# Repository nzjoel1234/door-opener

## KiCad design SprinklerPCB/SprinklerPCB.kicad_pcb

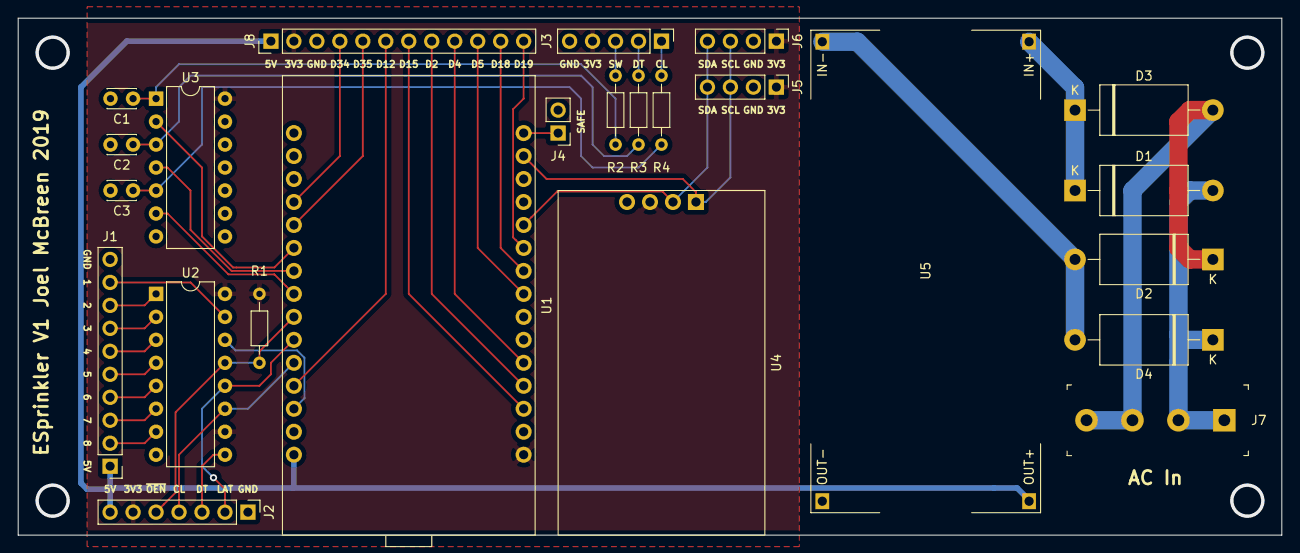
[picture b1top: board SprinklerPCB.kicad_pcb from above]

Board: 2 copper layers, 139.7 x 57.1 mm, 24 parts (0 on the bottom side), 41 nets.

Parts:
C1, C2, C3: 10n; C_Disc_D3.0mm_W2.0mm_P2.50mm
D1, D2, D3, D4: IN5404; D_DO-27_P15.24mm_Horizontal
J1: Conn_01x10_Male; PinHeader_1x10_P2.54mm_Vertical
J2: Conn_01x07_Male; PinHeader_1x07_P2.54mm_Vertical
J3: Conn_01x05_Male; PinHeader_1x05_P2.54mm_Vertical
J4: Conn_01x02_Male; PinHeader_1x02_P2.54mm_Vertical
J5, J6: Conn_01x04_Male; PinHeader_1x04_P2.54mm_Vertical
J7: Conn_01x04_Male; Term_Block_1x4_P5.08mm
J8: Conn_01x12_Male; PinHeader_1x12_P2.54mm_Vertical
R1: 47k; R_Axial_DIN0204_L3.6mm_D1.6mm_P7.62mm_Horizontal
R2, R3, R4: 10k; R_Axial_DIN0204_L3.6mm_D1.6mm_P7.62mm_Horizontal
U1: Esp32DevKitV1; ESP32_DEVKIT_V1
U2: 74HC595; DIP-16_W7.62mm
U3: 40106; DIP-14_W7.62mm
U4: DS3231Module; DS3231_RTC_Horizontal_4P_BatteryUp
U5: AdjustableStepDownConvertor

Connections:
24VAC+: D1.2, D4.1, J7.1, J7.2
24VAC-: D2.1, D3.2, J7.3, J7.4
+3V3: J2.6, J3.4, J5.1, J6.1, J8.2, R1.2, U1.16, U2.10, U2.16, U3.14, U4.3
+5V: J1.1, J2.7, J8.1, U1.15, U5.2
D2: J8.8, U1.19
D4: J8.9, U1.20
D5: J8.10, U1.23
D12: J8.6, U1.12
D15: J8.7, U1.18
D18: J8.11, U1.24
D19: J8.12, U1.25
D34: J8.4, U1.4
D35: J8.5, U1.5
GND: C1.2, C2.2, C3.2, J1.10, J2.1, J3.5, J4.2, J5.2, J6.2, J8.3, U1.14, U1.17, U2.8, U3.7, U4.4, U5.3
unnamed: C1.1, R2.1, U3.1
unnamed: C2.1, R3.1, U3.3
unnamed: C3.1, R4.1, U3.5
unnamed: D1.1, D3.1, U5.1
unnamed: D2.2, D4.2, U5.4
unnamed: J1.2, U2.7
unnamed: J1.3, U2.6
unnamed: J1.4, U2.5
unnamed: J1.5, U2.4
unnamed: J1.6, U2.3
unnamed: J1.7, U2.2
unnamed: J1.8, U2.1
unnamed: J1.9, U2.15
ROT_CL: J3.1, R4.2
ROT_CL_U: U1.8, U3.6
ROT_DT: J3.2, R3.2
ROT_DT_U: U1.7, U3.4
ROT_SW: J3.3, R2.2
ROT_SW_U: U1.6, U3.2
SAFE_MODE_SEL: J4.1, U1.30
SCL: J5.3, J6.3, U1.29, U4.1
SDA: J5.4, J6.4, U1.26, U4.2
SHIFTR_CLK: J2.4, U1.11, U2.11
SHIFTR_LAT: J2.2, U1.10, U2.12
SHIFTR_OVR: J2.3, U2.9
SHIFTR_SER: U1.13, U2.14
~SHIFTR_EN: J2.5, R1.1, U1.9, U2.13

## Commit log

2019-05-20 Add aws https client
2019-05-20 Remove aws credentials
2019-05-23 Update shadow reported state
2019-08-15 Enable auto-formatter
2019-08-15 Add basic mqtt example
2019-08-15 Begin work on display logic
2019-08-18 Add scroll arrows to menu
2019-09-09 Get rotary encoder and menu system working
2019-10-17 Get UI framework going
2019-10-24 Get manual runs working
2019-10-24 Add kicad files
2019-11-01 Allow start/stop from web
2019-11-25 Get MQTT subscription going
2020-04-26 Use windows line endings
2020-04-26 Add precompiling stage to setup script
2020-05-03 Get secure AWS mqtt client working
2020-05-08 Remove asyncio - and add screensaver
2020-05-15 Add report status functionality
2020-05-17 Support stopping zones via mqtt
2020-05-17 Add support for UtcOffset - to handle DST
2020-05-24 Fix stack depth exception
2022-06-03 Initial commit (based on uPy sprinkler)
2022-06-03 Show door state on local website
2022-06-05 Use polling instead of IRQ to avoid crashes
2022-06-05 Move AP credentials into config file
2022-06-05 Avoid attempting NTP sync until wifi is active
